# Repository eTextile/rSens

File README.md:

# rSens
## E-textile resistive sensors signal conditioning
### "What about the "E" in e-textiles?"

- Team project:
    - **Pauline Vierne** <pauline.vierne[AT]gmail.com>
    - **Maurin Donneaud** <maurin[AT]etextile.org>
- Repository: https://github.com/eTextile/rSens/tree/master
- Project web page: http://rsens.eTextile.org (TODO)
- License: CC-BY-SA (see the License file)

The rSens solution is a PCB that is useful for **signal conditioning** (scale, offset and filtering). It is placed between the Analog pin of your chosen microcontroller and a resistive sensor to improve its sensitivity.

It seemed to us that signal conditioning for e-textile sensors is often underestimate or ignored, and in the best case made as bricolage at software level (thinking of Arduino map() function or interpolating methods).

You will use this hardware e-textile PCB to zoom into the sensor's significant values without losing any resolution. Furthermore, rSens is able to pick up and amplify small resistance variations, so to exploit "weak signals" e.g. from micro-movements in the case of body-worn sensors.
It should also offer advantages of filtering out noise usually picked up by voltage dividers and correcting non-linear behaviours of resistive sensors.

The rSens PCB is built on top of a quad op-Amp and allows to connect and amplify two FSR (SMD version).

## Project content
- **Hardware_electronic**: PCB source files
- **Hardware_textile**: conductive textile PCB extension source files
- **Firmware**: read and graph the analog sensor values with [Arduino](https://www.arduino.cc/)

## Prerequisite
- The rSens PCB can be used in combination with any resistive sensors (custom or industrial)
- Adding R1 resistor to form an [optimised voltage divider](./Hardware#prerequisite)

**Keywords** `FSR`,`strain gages`,`e-textile`,`digital musical instruments`,`Do-It-Yourself`

# External links
- The Arduino [map() function](https://www.arduino.cc/reference/en/language/functions/math/map/)
- [A Comprehensive Review of Sensors and Instrumentation Methods in Devices for Musical Expression](./docs/A_Comprehensive_Review_of_Sensors_and_Instrumentat.pdf) (Article)
- op-Amp [datasheet](./Hardware_electronic/docs/datasheet_MCP6241.pdf)

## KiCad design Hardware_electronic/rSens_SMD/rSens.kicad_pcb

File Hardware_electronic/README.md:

# rSens / Hardware
## E-textile resistive sensors signal conditioning
### How to improve your resistive sensor (FSR) sensitivity

- Team project:
    - **Pauline Vierne** <pauline.vierne[AT]gmail.com>
    - **Maurin Donneaud** <maurin[AT]etextile.org>
- Repository: https://github.com/eTextile/rSens/tree/master
- Project web page: http://rsens.eTextile.org (TODO)
- License: CC-BY-SA (see the License file)

## Hardware folder
- This folder is contaning two versions of the project.
- **rSens_DIL** is a proof of concept that has been done for an e-Textile one stage performance.
- **rSens_SMD** is a redesign that has been done to optimize the form factor of the PCB and add a second amplification line.
- All source files are made with [KiCad](https://kicad.org/) 5.0.* 

## Prerequisite
Calculate the onboard DIL resistor **R1** using the included Python script [R1_calculator.py](../docs/R1_calculator.py)
This Python script will automatically calculate the resistor value that you need to get the best voltage divider efficiency.

To run this script you will first need to get your sensor characteristics by using a conventional multimeter. Then you will use these values as arguments to run the script :

1. **First Arg** is the resistivity (in Ohm) of your FSR sensor at rest
2. **Second Arg** is the resistivity (in Ohm) of your FSR sensor at maximum effort

```
cd rSens/docs
```
```
python R1_calculator.py 200 3450
```

3. If you run the script with the above arguments you must get the following result

```
R1 = 830 Ohm
Efficiency = 61.19 %
```
5. After all you can solder the calculated R1 resistor onto the PCB

## BOM rSens_SMD
| Référence                | Def (Kicad components names)                      | Quantity | Value        |
|:-------------------------|:--------------------------------------------------|----------|:-------------|
|  R6,R8,R9,R7,R5,R4,R3,R2 | R_0805_2012Metric_Pad1.20x1.40mm_HandSolder       |    8     |  10K	     |
|  R1,R10                  | R_Axial_DIN0309_L9.0mm_D3.2mm_P12.70mm_Horizontal |    2     |  USER_DEFINE |
|  C2,C3,C1                | C_0805_2012Metric_Pad1.18x1.45mm_HandSolder       |    3     |  100N	     |
|  RV2,RV1,RV3,RV4         | Potentiometer_Vishay_TS53YJ_Vertical              |    4     |  100K	     |
|  U2                      | TSSOP-14_4.4x5mm_P0.65mm                          |    1     |  MCP6244	 |

## PCB specifications
- **Base Material** : FR-4 TG130
- **No. of Layers** : 2 layers
- **PCB Dimensions** : 70mm / 76mm
- **No. of Different Designs** : 1
- **PCB Thickness** : 1.00 mm
- **PCB Color** : Black
- **Surface Finish** : ENIG
- **Minimum Solder Mask Dam** : 0.4mm
- **Copper Weight** : 1oz.
- **Minimum Drill Hole Size** : 0.3mm
- **Trace Width / Spacing** : 6/6 mil
- **Plated Half-holes / Castellated Holes** : Yes
- **Impedance Control** : No

# External links
- [A Comprehensive Review of Sensors and Instrumentation Methods in Devices for Musical Expression](../docs/A_Comprehensive_Review_of_Sensors_and_Instrumentat.pdf) (Article)
- [Voltage divider - wikipedia](https://en.wikipedia.org/wiki/Voltage_divider)
- [op-Amp datasheet](./docs/datasheet_MCP6241.pdf)

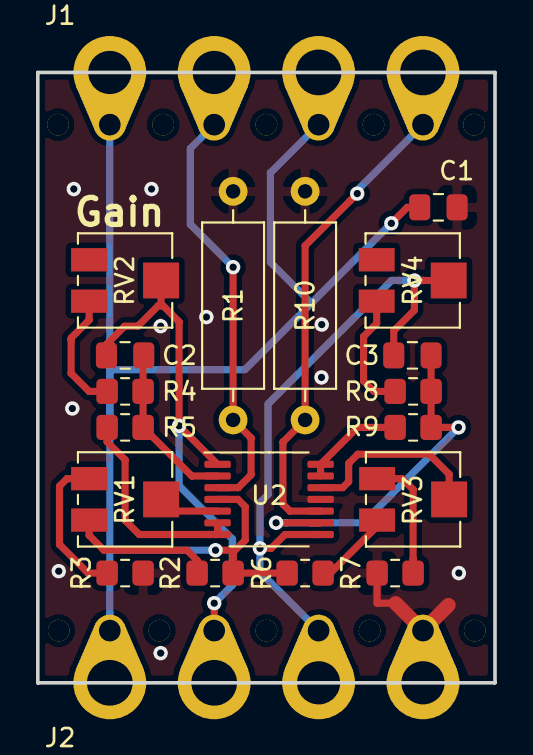
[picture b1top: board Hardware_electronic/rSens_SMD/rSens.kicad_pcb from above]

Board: 2 copper layers, 25.4 x 33.9 mm, 20 parts (0 on the bottom side), 18 nets.

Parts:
C1, C2, C3: 100N; C_0805_2012Metric_Pad1.18x1.45mm_HandSolder
J1, J2: Conn_01x04; rSens_Pad_1x04
R1, R10: 10K; R_Axial_DIN0309_L9.0mm_D3.2mm_P12.70mm_Horizontal
R2, R3, R4, R5, R6, R7, R8, R9: 10K; R_0805_2012Metric_Pad1.20x1.40mm_HandSolder
RV1, RV2, RV3, RV4: 100K; Potentiometer_Vishay_TS53YJ_Vertical
U2: MCP6244; TSSOP-14_4.4x5mm_P0.65mm

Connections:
GND: C1.2, J2.1, R1.2, R3.2, R7.2, R10.2, U2.11
unnamed: C2.2, R4.2, R5.1, U2.2
unnamed: C3.2, R8.2, R9.1, U2.9
unnamed: R2.2, RV1.1
unnamed: R3.1, RV1.3
unnamed: R4.1, RV2.1
unnamed: R5.2, U2.6, U2.7
unnamed: R6.2, RV3.1
unnamed: R7.1, RV3.3
unnamed: R8.1, RV4.1
unnamed: R9.2, U2.13, U2.14
unnamed: RV1.2, U2.5
unnamed: RV3.2, U2.12
SENSOR_INPUT_A: J1.2, R1.1, U2.3
SENSOR_INPUT_B: J1.4, R10.1, U2.10
VCC: C1.1, J1.1, J1.3, J2.4, R2.1, R6.1, U2.4
VOLTAGE_OUTPUT_A: C2.1, J2.3, RV2.2, U2.1
VOLTAGE_OUTPUT_B: C3.1, J2.2, RV4.2, U2.8

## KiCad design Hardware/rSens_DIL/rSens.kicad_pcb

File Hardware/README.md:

# rSens / Hardware
## E-textile resistive sensors signal conditioning
### How to improve your resistive sensor (FSR) sensitivity

- Team project:
    - **Pauline Vierne** <pauline.vierne[AT]gmail.com>
    - **Maurin Donneaud** <maurin[AT]etextile.org>
- Repository: https://github.com/eTextile/rSens/tree/master
- Project web page: http://rsens.eTextile.org (TODO)
- License: CC-BY-SA (see the License file)

## Hardware folder
- This folder is contaning two versions of the project.
- **rSens_DIL** is a proof of concept that has been done for an e-Textile one stage performance.
- **rSens_SMD** is a redesign that has been done to optimize the form factor of the PCB and add a second amplification line.
- All source files are made with [KiCad](https://kicad.org/) 5.0.* 

## Prerequisite
Calculate the onboard DIL resistor **R1** using the included Python script [R1_calculator.py](../docs/R1_calculator.py)
This Python script will automatically calculate the resistor value that you need to get the best voltage divider efficiency.

To run this script you will first need to get your sensor characteristics by using a conventional multimeter. Then you will use these values as arguments to run the script :

1. **First Arg** is the resistivity (in Ohm) of your FSR sensor at rest
2. **Second Arg** is the resistivity (in Ohm) of your FSR sensor at maximum effort

```
cd rSens/docs
```
```
python R1_calculator.py 200 3450
```

3. If you run the script with the above arguments you must get the following result

```
R1 = 830 Ohm
Efficiency = 61.19 %
```
5. After all you can solder the calculated R1 resistor onto the PCB

## BOM rSens_SMD
| Référence                | Def                                               | Quantity | Value        |
|:-------------------------|:--------------------------------------------------|----------|:-------------|
|  R6,R8,R9,R7,R5,R4,R3,R2 | R_0805_2012Metric_Pad1.20x1.40mm_HandSolder       |    8     |  10K	     |
|  R1,R10                  | R_Axial_DIN0309_L9.0mm_D3.2mm_P12.70mm_Horizontal |    2     |  USER_DEFINE |
|  C2,C3,C1                | C_0805_2012Metric_Pad1.18x1.45mm_HandSolder       |    3     |  100N	     |
|  RV2,RV1,RV3,RV4         | C_0805_2012Metric_Pad1.18x1.45mm_HandSolder       |    4     |  100K	     |
|  U2                      | TSSOP-14_4.4x5mm_P0.65mm                          |    1     |  MCP6244	 |

## PCB specifications
- **Base Material** : FR-4 TG130
- **No. of Layers** : 2 layers
- **PCB Dimensions** : 70mm / 76mm
- **No. of Different Designs** : 1
- **PCB Thickness** : 1.00 mm
- **PCB Color** : Black
- **Surface Finish** : ENIG
- **Minimum Solder Mask Dam** : 0.4mm
- **Copper Weight** : 1oz.
- **Minimum Drill Hole Size** : 0.3mm
- **Trace Width / Spacing** : 6/6 mil
- **Plated Half-holes / Castellated Holes** : Yes
- **Impedance Control** : No

# External links
- Article : A Comprehensive Review of Sensors and Instrumentation Methods in Devices for Musical Expression
- op-Amp datasheet : TODO
- [Voltage divider](https://en.wikipedia.org/wiki/Voltage_divider)

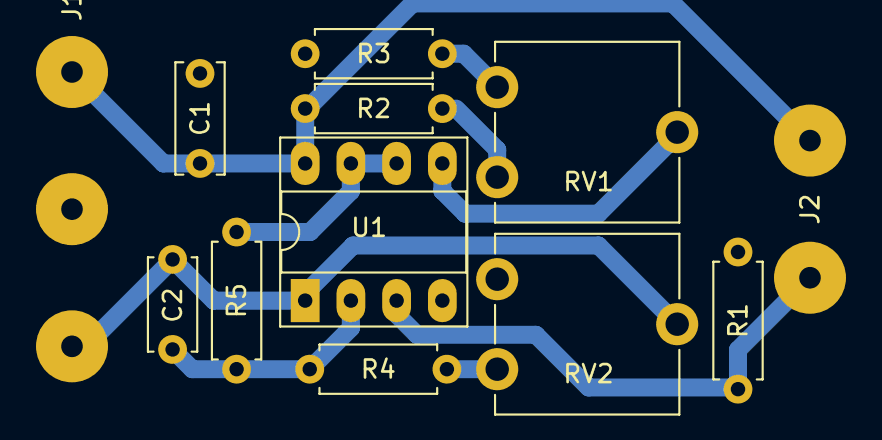
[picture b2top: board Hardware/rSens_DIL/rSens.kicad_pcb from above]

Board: 2 copper layers, 12 parts (0 on the bottom side), 10 nets.

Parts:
C1: 100N; C_Disc_D6.0mm_W2.5mm_P5.00mm
C2: 100N; C_Disc_D5.0mm_W2.5mm_P5.00mm
J1: TO_ARDUINO; custom_SolderWirePad_1x03
J2: RESISTIVE_SENSOR; custom_SolderWirePad_1x02
R1: 100K; R_Axial_DIN0207_L6.3mm_D2.5mm_P7.62mm_Horizontal
R2, R3, R4, R5: 10K; R_Axial_DIN0207_L6.3mm_D2.5mm_P7.62mm_Horizontal
RV1, RV2: 100K; Potentiometer_ACP_CA9-V10_Vertical
U1: MCP602; DIP-8_W7.62mm_Socket_LongPads

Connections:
GND: C1.2, J1.2, R1.2, R3.2, U1.4
unnamed: C2.2, R4.2, R5.1, U1.2
unnamed: R2.2, RV1.1
unnamed: R3.1, RV1.3
unnamed: R4.1, RV2.1
unnamed: R5.2, U1.6, U1.7
unnamed: RV1.2, U1.5
OUTPUT: C2.1, J1.1, RV2.2, U1.1
VCC: C1.1, J1.3, J2.1, R2.1, U1.8
VOLTAGE_OUTPUT: J2.2, R1.1, U1.3

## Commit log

2021-01-04 Added Arduino code
2021-01-04 Updated script name
2021-01-04 Updated script / print out the best result
2021-01-04 Removed unused Python script arg
2021-01-05 Added picture
2021-01-05 Added picture file
2021-01-05 FIX picture link
2021-01-05 Updated picture
2021-01-05 fixed grammar mistakes
2021-01-05 better meaning
2021-01-05 added more informations
2021-01-06 Subtitle update
2021-01-06 FIX 3D
2021-03-04 Routing in progress
2021-03-04 Routing done
2021-03-05 Added GERBER
2021-03-05 Updated PCB holes size
2021-03-05 Updated pict link
2021-03-05 FIX link
2021-03-05 Added opAmp datasheet
2021-03-06 Added rSens textile pad_00
2021-03-06 Updated textile Pad_00
2021-03-06 CleanUP
2021-04-01 Updated PCB & GERBER for production & README
2021-04-01 CleanUp schematics
2021-04-01 Export rSens_schematics.jpg
2021-04-20 added Kicad to Def
2022-06-06 added parentheses
